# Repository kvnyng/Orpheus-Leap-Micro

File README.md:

# Orpheus Leap Micro

During the summer of 2020, Hack Club hosted [*Summer of Making*](https://summer.hackclub.com)! It was three months of non-stop hardware hacking! They partnered with GitHub, to give out $50,000 worth of hardware grants and help makers like me!

With that said, to further rep and hype up Summer Of Making, I was asked to design a general-purpose Arduino PCB to commerate the event. With gracious funding from Github and Adafruit, the Orpheus Leap was put into production and 500 were made, shipped, and received by all Summer of Making Hack Clubbers!

This repo holds the Gerber, Eagle files, and documentation for the board. 

# Design

The Orpheus Leap is based off of the Arduino compatible Pro Micro design. Powered by the ATmega32U4, the main features of Orpheus Leap are as follows:

### Features

**Pins**
* 20 I/O pins 
* 7 PWM Channels
* 12 Analog Inputs

**Memory**
* 32 KB Flash Memory (of which 4 KB used for bootloader)
* 2.5 KB SRAM
* 1 KB EEPROM

**Power**
* 5V Logic
* 7-12V input range with VIN pin
* 40 mA output per I/O pin

**Miscellaneous**
* Built-in USB Support (no need for programmer)
* Can act as USB device (keyboard, mouse, game controller, etc)
* A beautiful Orpheus shaped PCB
* ICSP headers for ICSP programming

<!-- # Photos -->
<hr width="50%">

**PCB designed by Kevin Yang, 2020. Supported by Hack Club & GitHub.**

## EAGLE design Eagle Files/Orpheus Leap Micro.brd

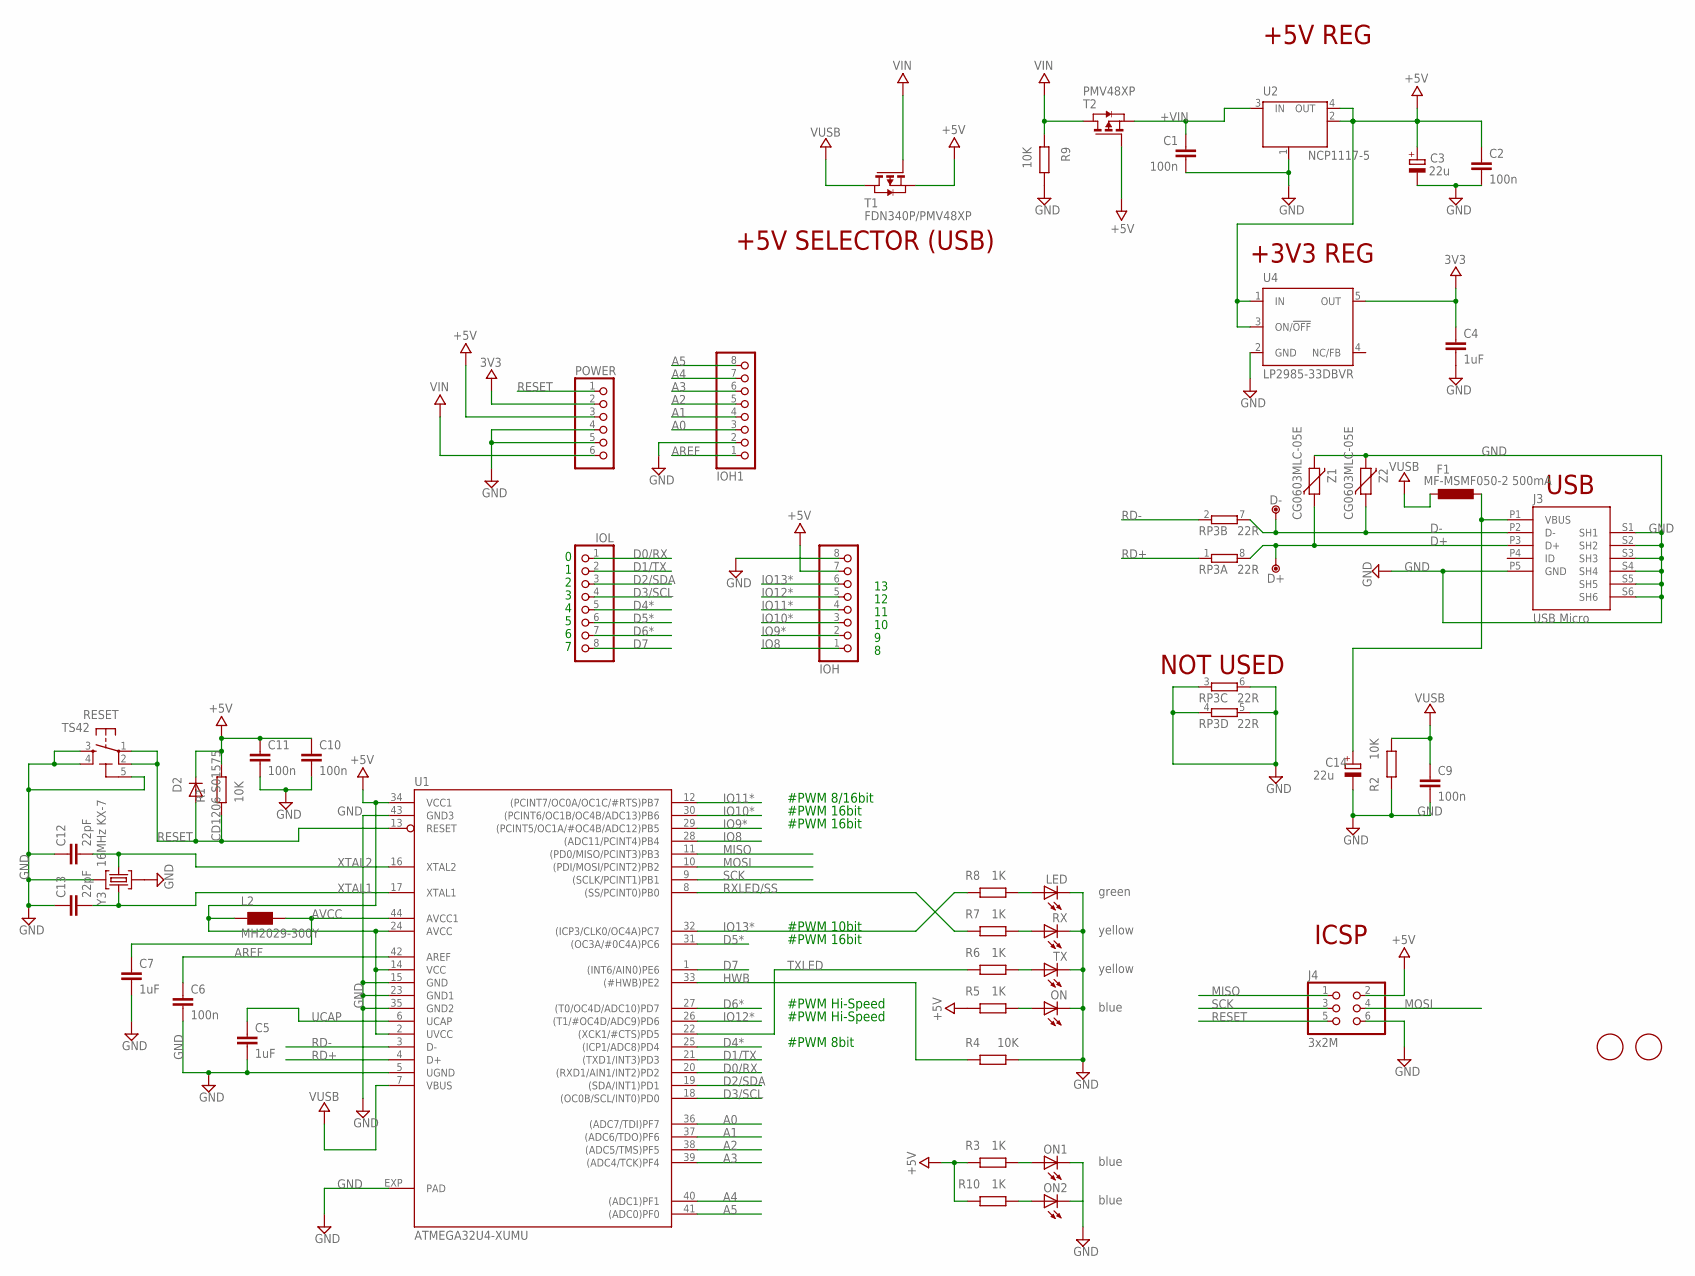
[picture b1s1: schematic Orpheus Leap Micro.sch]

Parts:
C1, C2, C6, C9, C10, C11: 100n; C0402
C3, C14: 22u; SMC_B
C4, C5, C7: 1uF; C0402
C12, C13: 22pF; C0402
D2: CD1206-S01575; MINIMELF
D+: DNP; TP-1.00MM
D-: DNP; TP-1.00MM
F1: MF-MSMF050-2 500mA; L1812
IOH, IOH1: PINHD-1X8; 1X08
IOL: PINHD-1X8; 1X08
J3: USB Micro; CON2_USB_MICRO_B_AT
J4: 3x2M; 2X03
L2: MH2029-300Y; 0805
LED: green; CHIPLED_0805
ON, ON1, ON2: blue; CHIPLED_0805
POWER: PINHD-1X6; 1X06
R1, R2, R4, R9: 10K; R0402
R3, R5, R6, R7, R8, R10: 1K; R0402
RESET: TS42
RP3: 22R; CAY16
RX: yellow; CHIPLED_0805
T1: FDN340P/PMV48XP; SOT-23
T2: PMV48XP; SOT-23
TX: yellow; CHIPLED_0805
U1: ATMEGA32U4-XUMU; QFN44ML7X7
U2: NCP1117-5; SOT223
U4: LP2985-33DBVR; SOT23-DBV
U$37, U$53: DNP; FD-1-1.5
Y3: 16MHz KX-7; CRYSTAL-3.2-2.5
Z1, Z2: CG0603MLC-05E; CT/CN0603

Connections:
3V3: C4.1, POWER.2, U4.5 (OUT)
+5V: C2.1, C3.+, C10.1, C11.1, D2.C, IOH.7, J4.2, L2.1, POWER.3, R1.1, R3.1, R5.1, R10.1, T1.2 (S), T2.3 (G), U1.2 (UVCC), U1.14 (VCC), U1.24 (AVCC), U1.34 (VCC1), U2.2 (OUT), U2.4 (OUT), U4.1 (IN), U4.3 (ON/!OFF)
+VIN: C1.1, T2.2 (S), U2.3 (IN)
A0: IOH1.3, U1.36 ((ADC7/TDI)PF7)
A1: IOH1.4, U1.37 ((ADC6/TDO)PF6)
A2: IOH1.5, U1.38 ((ADC5/TMS)PF5)
A3: IOH1.6, U1.39 ((ADC4/TCK)PF4)
A4: IOH1.7, U1.40 ((ADC1)PF1)
A5: IOH1.8, U1.41 ((ADC0)PF0)
AREF: C6.1, IOH1.1, U1.42 (AREF)
AVCC: C7.1, L2.2, U1.44 (AVCC1)
D0/RX: IOL.1, U1.20 ((RXD1/AIN1/INT2)PD2)
D1/TX: IOL.2, U1.21 ((TXD1/INT3)PD3)
D2/SDA: IOL.3, U1.19 ((SDA/INT1)PD1)
D3/SCL: IOL.4, U1.18 ((OC0B/SCL/INT0)PD0)
D4*: IOL.5, U1.25 ((ICP1/ADC8)PD4)
D5*: IOL.6, U1.31 ((OC3A/#0C4A)PC6)
D6*: IOL.7, U1.27 ((T0/OC4D/ADC10)PD7)
D7: IOL.8, U1.1 ((INT6/AIN0)PE6)
D+: D+.X, J3.P3 (D+), RP3.8 (2), Z1.1
D-: D-.X, J3.P2 (D-), RP3.7 (2), Z2.1
GND: C1.2, C2.2, C3.-, C4.2, C5.2, C6.2, C7.2, C9.2, C10.2, C11.2, C12.1, C13.1, C14.-, IOH.8, IOH1.2, J3.P5 (GND), J3.S1 (SH1), J3.S2 (SH2), J3.S3 (SH3), J3.S4 (SH4), J3.S5 (SH5), J3.S6 (SH6), J4.6, LED.C, ON.C, ON1.C, ON2.C, POWER.4, POWER.5, R2.1, R4.2, R9.1, RESET.3, RESET.4, RESET.5 (5-GND), RP3.3 (1), RP3.4 (1), RP3.5 (2), RP3.6 (2), RX.C, TX.C, U1.5 (UGND), U1.15 (GND), U1.23 (GND1), U1.35 (GND2), U1.43 (GND3), U1.EXP (PAD), U2.1 (GND/ADJ), U4.2 (GND), Y3.2 (GND), Y3.4 (GND), Z1.2, Z2.2
HWB: R4.1, U1.33 ((#HWB)PE2)
IO8: IOH.1, U1.28 ((ADC11/PCINT4)PB4)
IO9*: IOH.2, U1.29 ((PCINT5/OC1A/#OC4B/ADC12)PB5)
IO10*: IOH.3, U1.30 ((PCINT6/OC1B/OC4B/ADC13)PB6)
IO11*: IOH.4, U1.12 ((PCINT7/OC0A/OC1C/#RTS)PB7)
IO12*: IOH.5, U1.26 ((T1/#OC4D/ADC9)PD6)
IO13*: IOH.6, R8.1, U1.32 ((ICP3/CLK0/OC4A)PC7)
MISO: J4.1, U1.11 ((PD0/MISO/PCINT3)PB3)
MOSI: J4.4, U1.10 ((PDI/MOSI/PCINT2)PB2)
unnamed: ON1.A, R3.2
unnamed: R7.2, RX.A
unnamed: ON.A, R5.2
unnamed: R6.2, TX.A
unnamed: ON2.A, R10.2
unnamed: LED.A, R8.2
RD+: RP3.1, U1.4 (D+)
RD-: RP3.2 (1), U1.3 (D-)
RESET: D2.A, J4.5, POWER.1, R1.2, RESET.1, RESET.2, U1.13 (RESET)
RXLED/SS: R7.1, U1.8 ((SS/PCINT0)PB0)
SCK: J4.3, U1.9 ((SCLK/PCINT1)PB1)
TXLED: R6.1, U1.22 ((XCK1/#CTS)PD5)
UCAP: C5.1, U1.6 (UCAP)
VIN: POWER.6, R9.2, T1.3 (G), T2.1 (D)
VUSB: C9.1, F1.2, R2.2, T1.1 (D), U1.7 (VBUS)
VUSBD: C14.+, F1.1, J3.P1 (VBUS)
XTAL1: C13.2, U1.17 (XTAL1), Y3.3 (C2)
XTAL2: C12.2, U1.16 (XTAL2), Y3.1 (C1)

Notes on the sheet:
+5V REG
ICSP
USB
+5V SELECTOR (USB)
NOT USED
+3V3 REG
#PWM 8bit
#PWM Hi-Speed
#PWM 16bit
#PWM 10bit
#PWM 8/16bit

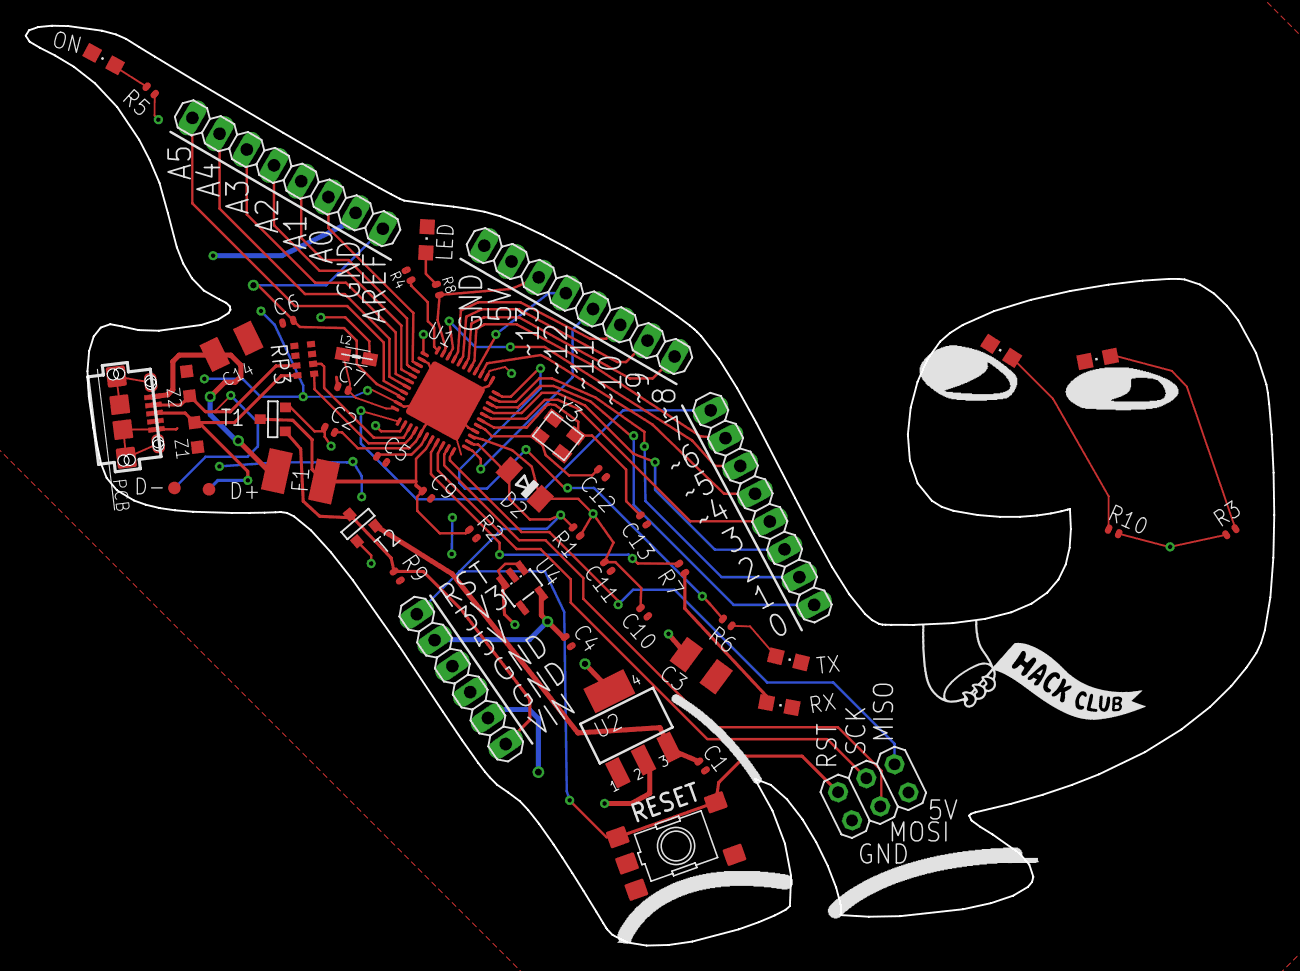
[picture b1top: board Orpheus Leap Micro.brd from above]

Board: 2 copper layers, 100.8 x 74.2 mm, 52 parts (0 on the bottom side), 49 nets.

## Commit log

2020-08-28 added files?
2020-08-28 add site
2020-09-02 🎨 just wanted to fix linking to external files and fixing the overflow that was occurring
2020-09-02 [ImgBot] Optimize images
    *Total -- 622.02kb -> 321.15kb (48.37%)
    /Images/Orpheus Redraw.png -- 70.69kb -> 24.91kb (64.76%)
    /Images/Orpheus Leap Original.png -- 16.43kb -> 7.01kb (57.32%)
    /Images/Orpheus Leap PCB (Bottom).png -- 133.33kb -> 61.66kb (53.75%)
    /Images/Orpheus Leap PCB (Top).png -- 215.84kb -> 105.85kb (50.96%)
    /Images/Arduino Micro Schematic.png -- 185.73kb -> 121.71kb (34.47%)
2020-09-02 one more fix with the js
2020-09-02 add case
2020-09-15 added .dwg
2020-10-02 Update README.md
    add some stuff Kevin left out, which are pretty critical to the purpose of these specially shaped Arduino boards.

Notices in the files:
parts and their libraries:
Arduino-utility: Copyright (c) 2016-2017 Arduino LLC.  All right reserved.
